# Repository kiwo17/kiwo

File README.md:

# Kiwo Player
kiwo is a small portable MP3 player.
It can also be used as a very cool looking keychain!

[Image coming sooooooooooooooooooooooooooooooooooooooooooooon]

Insert you favorite songs into micro SD card, plug it in the kiwo player, click play and enjoy!

## About the Project

I got the inspiration from a reel that I saw on Instagram, a small MP3 player on a prefboard. Back then I hadn't even realized that I could build something
that cool by myself. I've loved music and building things since a kid and I thought that I should try to make something that connects both. Similar motivation to my previous
project, the midi keypad from Kai Pereira. Music is never to much!

If I am making something that looks awesome might as well make it visible to others. So I came up with the Idea of making it a keychain. 
Now you can listen to music anywhere you want, as long you have the kiwo player and headphones with you!

## Process

In the beginning I researched a lot about MP3 players. How they work, their connections, their components and its functions etc.
It was quite confusing but I learned tons of new knowledge in this area.

Some things weren't as useful to research, such as how KiCad works, because you learn it better by experimenting.

Then I started to chose my components, which didn't take too long. MP3 player usually have the same structure.
Right after I started the wiring but then the first problems popped up. 

### Difficulties

- Symbols and footprints
  Symbols and footprints for some of the components I wanted to use weren't available in the KiCad library or online so I had to learn how to create those myself...

- Wiring
  This still overwhelms me now. This process (at least for me) took me a lot of time. I had to learn about different protocols, connections and functions. Then needed
  to research about very component to know which pins to use and how to connect them. Lastly I had to fix tons of mistakes.

### Schematic 

### Front Cu layer

### Back Cu layer

### Currently working on ... 

- routing

### Next steps ...

- Firmware

## Do it yourself!

I will write a guide for you to try making your own MP3 and customize it as you wish!

It will be available as soon as possible...

## BOM

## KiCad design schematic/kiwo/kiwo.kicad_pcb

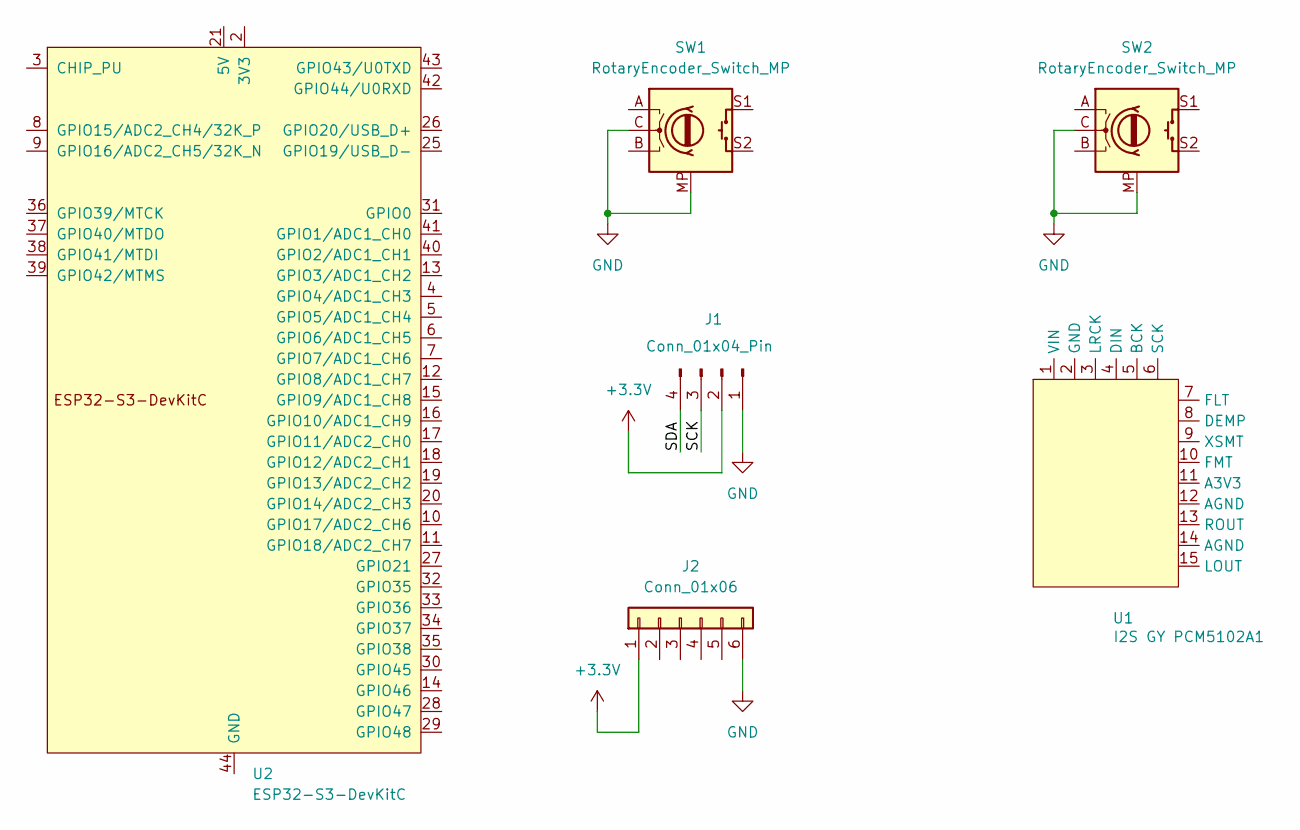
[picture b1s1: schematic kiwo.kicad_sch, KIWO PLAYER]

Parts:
J1: Conn_01x04_Pin; Display_128x64_096_I2C
J2: Conn_01x06; MicroSD_SPI_Module_20x20
SW1, SW2: RotaryEncoder_Switch_MP; RotaryEncoder_Alps_EC11E-Switch_Vertical_H20mm
U1: I2S GY PCM5102A1; GY_PCM5102A
U2: ESP32-S3-DevKitC

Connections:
+3.3V: J1.2, J2.1
/SCK: J1.3
/SDA: J1.4
GND: J1.1, J2.6, SW1.C, SW1.MP, SW2.C, SW2.MP
unnamed: U2.1 (3V3), U2.2 (3V3)
unnamed: U2.22 (GND), U2.23 (GND), U2.24 (GND), U2.44 (GND)

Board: 2 copper layers, 6 parts (0 on the bottom side), 4 nets, no tracks yet.

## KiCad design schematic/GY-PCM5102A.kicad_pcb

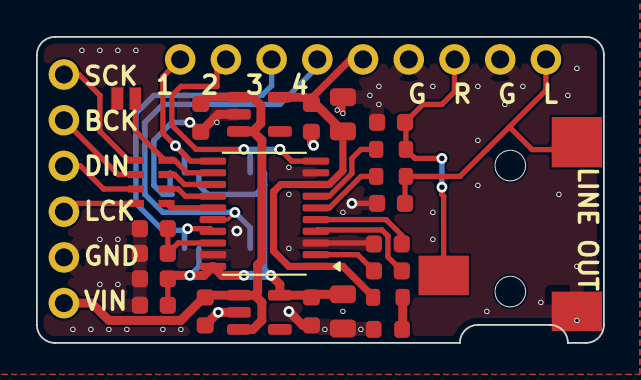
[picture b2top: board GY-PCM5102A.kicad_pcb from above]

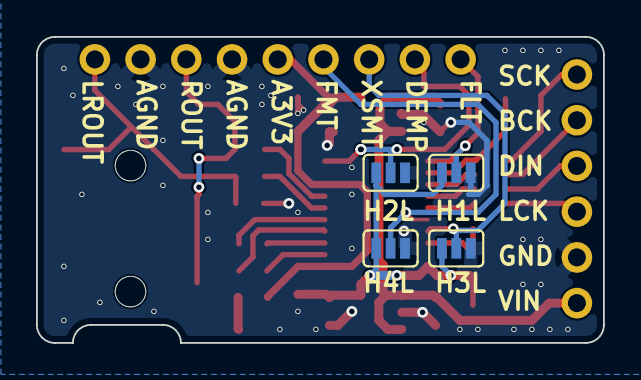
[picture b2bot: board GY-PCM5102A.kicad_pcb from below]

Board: 2 copper layers, 31.5 x 17.0 mm, 30 parts (4 on the bottom side), 25 nets.

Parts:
C1, C2, C4, C6, C12, C14: 100n; C_0603_1608Metric
C3, C5: 10u; C_0805_2012Metric
C7, C8, C9, C10: 2.2u; C_0603_1608Metric
C11, C13: 10u; C_0603_1608Metric
D1: Red; LED_0603_1608Metric
H1L, H2L, H3L, H4L: SolderJumper-3_P1.3mm_Open_Pad0.55x1.15mm
J1: M-BUS; PinHeader_1x06_P2.54mm_Vertical
J2: FUN_AND_OUT; PinHeader_1x09_P2.54mm_Vertical
J3: AudioJack3; Jack_3.5mm_CUI_SJ-3523-SMT_Horizontal
JP1: SolderJumper_2_Open; SolderJumper-2_P1.3mm_Open_Pad1.0x1.5mm
R1: 1K; R_0603_1608Metric
R2, R3: 470; R_0603_1608Metric
RN1: 22; R_Array_Concave_4x0603
U1: PCM5102A; TSSOP-20_4.4x6.5mm_P0.65mm
U2, U3: ME6211C33M5; SOT-23-5

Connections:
/AVDD: C2.1, C3.1, J2.5 (A3V3), R1.2, U1.1 (CPVDD), U1.8 (AVDD), U2.5 (V_{OUT})
/BCK: J1.5 (BCK), RN1.6 (R3.2)
/DEMP: H2L.2 (C), J2.2 (DEMP), U1.10 (DEMP)
/DIN: J1.4 (DIN), RN1.7 (R2.2)
/DVDD: C5.1, C6.1, C13.1, C14.2, H1L.1 (A), H2L.1 (A), H3L.1 (A), H4L.1 (A), U1.20 (DVDD), U3.5 (V_{OUT})
/FLT: H1L.2 (C), J2.1 (FLT), U1.11 (FLT)
/FMT: H4L.2 (C), J2.4 (FMT), U1.16 (FMT)
/LRCK: J1.3 (LRCK), RN1.8 (R1.2)
/OUTL: C9.1, J2.9 (LOUT), J3.T, R2.2
/OUTR: C10.1, J2.7 (ROUT), J3.R, R3.2
/SCK: J1.6 (SCK), RN1.5 (R4.2)
/VIN: C1.1, C4.1, J1.1 (VIN), U2.1 (V_{IN}), U2.3 (CE), U3.1 (V_{IN}), U3.3 (CE)
/XSMT: H3L.2 (C), J2.3 (XSMT), U1.17 (XSMT)
GND: C1.2, C2.2, C3.2, C4.2, C5.2, C6.2, C7.2, C9.2, C10.2, C11.2, C12.2, C13.2, C14.1, D1.1 (K), H1L.3 (B), H2L.3 (B), H3L.3 (B), H4L.3 (B), J1.2 (GND), J2.6 (AGND), J2.8 (AGND), J3.S, JP1.1 (A), U1.3 (CPGND), U1.9 (AGND), U1.19 (DGND), U2.2 (V_{SS}), U3.2 (V_{SS})
unnamed: D1.2 (A), R1.1
unnamed: JP1.2 (B), RN1.4 (R4.1), U1.12 (SCK)
unnamed: RN1.1 (R1.1), U1.15 (LRCK)
unnamed: RN1.2 (R2.1), U1.14 (DIN)
unnamed: RN1.3 (R3.1), U1.13 (BCK)
unnamed: C8.2, U1.4 (CAPM)
unnamed: C8.1, U1.2 (CAPP)
unnamed: C11.1, C12.1, U1.18 (LDOO)
unnamed: R2.1, U1.6 (OUTL)
unnamed: R3.1, U1.7 (OUTR)
unnamed: C7.1, U1.5 (VNEG)
